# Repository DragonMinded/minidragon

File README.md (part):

# MiniDragon

Schematics, hardware simulator and software files for the MiniDragon CPU. This is a from-scratch CPU that I designed and am implementing using transistors, capacitors, resistors and diodes. The goal is to make an 8-bit CPU that could be used for general-purpose computing. There are a lot of toy instruction sets floating around on the web. I chose instead to design my own, loosely based off of the PDP and 6502. It is a single accumulator design with a pair of 16-bit stack pointers and a pair of temporary 8-bit registers. Instructions are 8 bits, operands are 8 bits from memory, temporary registers or immediate, and running software can access all 16 bits of memory available to the CPU. Eventually, I want the assembled CPU along with some external RAM, ROM and a serial interface chip to be self-hosting. For that, the boot ROM includes a serial montor with a line assembler and disassembler.

## Layout

The layout is separated into logical components:

 * Microcode counter. This keeps track of what microcode in the current instruction we are operating on.
 * Instruction decoder logic. This consists of an instruction register and a series of ROM boards made out of jumpers. This uses the microcode counter as well as its own internal combinatorial logic to select one instruction and output control signals to the rest of the CPU.
 * Registers. These exist on various busses, and their input/output is controlled by the instruction decoder logic's control signals.
 * Constant circuits. These can output either a zero or an immediate value sign extended from the current instruction register. Their operation is controlled by the instruction decoder's control signals.
 * ALU. This is built out of a series of smaller components on its own internal bus. Selection of which operation as well as which input is controlled via the instruction decoder logic's control signals.
 * Flags handling. This consists of a few registers to hold flags generated by the ALU and put them on the data bus when appropriate. This is controlled via the control signal lines much like the rest of the non-instruction decoder components.
 * Memory interface. This provides the glue so that the CPU can be seen as having a set of address and data lines as well as an output enable and write enable line, much like a traditional non-SOC CPU.

### Internal Busses

 * 16-bit data bus. Most registers can only read from or write to the lower 8 bits of this bus, but some can also output their value to the upper 8 bits. Various 16-bit registers are able to read the entire 16-bit bus, and this is how the upper bits of the instruction pointer and stack pointers can be read. The lower 8 bits of this will feed the external data IO lines.
 * 16-bit address bus. This feeds the external address requests by the CPU and is driven by both the instruction pointer and stack pointers.
 * 16-bit ALU source bus. This allows the ALU A source to be controlled, so that various 16-bit registers we want to add/subtract from don't need to be placed in a temporary location.

### Registers

 * 16-bit instruction pointer register (IP), holding the address of the current instruction in memory. Its value can be placed on the address bus or ALU input bus and it can read from the data bus. Software can jump relative to the current instruction, as well as pushing the current IP to the stack (controlled by the PC combined register), pop the IP from the stack or jump to an immediate 16 bit address.
 * 8-bit instruction register (IR), holding the current instruction that was fetched from memory. It is write-only and feeds microcode decoding logic, but can read from the data bus. Software cannot directly set this, but memory is modifiable so self-modifying code is possible.
 * 8-bit accumulator register (A), holding the current accumulated result. It can read from and write to the data bus, and it can output to the ALU input bus. Many instructions available to software can directly manipulate this register. Its value can be moved to and from the P and C registers as well as added to the combined PC register, allowing it to be used for indirect memory address modes as well.
 * 8-bit ALU temporary register (B), holding a temporary value from the bus. It can read from and write to the data bus. Its output is also hardcoded to the second input of the ALU. Software has no capability to modify this register and it is used by various microcodes to accomplish virtually all CPU operations. When the ALU is operating on a 16-bit number, the B register will be sign-extended to 16 bits.
 * 8-bit memory page register (P) and 8-bit memory cell register (C), together holding a 16-bit address. The P and C registers can individually read from the data bus, and the combined PC value can be output to the address bus or the ALU input bus. Software can write to the P and C registers from the A register and can use the combined PC register contents to load from and store to memory. Some ALU operations allow the memory address pointed at by the PC register to be used as an operand for ALU operations against the accumulator (A). The current value of the instruction pointer (IP) can be pushed to or popped from memory referred to by this register. The current value of the shadow PC combined register can also be pushed to or popped from memory referred to by this register.
 * 8-bit shadow page register (SP) and 8-bit shadow cell register (SC), together holding a 16-bit address referred to as SPC. This is not directly addressable, but its current value can be pushed to or popped from the location pointed at by the PC register, and a SWAP instruction allows software to swap the PC and SPC registers.
 * 8-bit CPU data register (D), holding temporary values when the CPU is pushing or popping a 16-bit value off of the stack (PC). We could use the A register for this, but I wanted to make sure that the accumulator was not clobbered when performing stack operations. This is not user readable or writeable.
 * 8-bit temporary registers (U and V), available to the programmer for various operations. These can be moved to from A, swapped to from A or each other, loaded from and stored to memory, and can be used as operands for ALU operations against the accumulator (A).
 * 3-bit flags register, containing a carry flag (CF), a zero flag (ZF) and a shadow PC flag (PC). Software cannot directly set or clear the carry or zero flags, but both carry and zero flags are set appropriately when carrying out any ALU-based operation which sources from and stores to the A register. It is not directly readable by software but there exist skip instructions that allow software to conditionally execute a particular instruction if either CF or ZF is set or cleared. Additionally, several ALU operations allow using the carry flag as an input to chain operations together for 16 and 32 bit arithmetic. The PC flag is toggleable using a special SWAP instruction.

### Instructions

 * JRI - Jump relative to immediate sign-extended + 1. Assembler also supports labels. Can jump 32 forward or backward relative to next instruction. Specifically designed such that "JRI 0" jumps to the next instruction and is encoded as all zeros.
 * LOADI - Load immediate stored in next memory cell to A. Can load any 8-bit value. Skips over that value after executing since it is not a valid instruction.
 * ADDI - Add immediate sign-extended to A, no carry. Can add values between -32 and 31. Affects ZF and CF.
 * INV - Bitwise invert A. Affects ZF and CF.
 * NEG - Twos compliment negate A register. Affects ZF and CF, as if it was implemented as an "INV" followed by an "ADDI 1".
 * SHL - Shift A left by 1, setting the bottom bit to 0, set carry to top bit shifted out. Affects ZF and CF.
 * SHR - Shift A right by 1, setting the top bit to 0, set carry to bottom bit shifted out. Affects ZF and CF.
 * RCL - Shift A left by 1, setting bottom bit to the carry flag, set carry to top bit shifted out. Affects ZF and CF.
 * RCR - Shift A right by 1, setting top bit to the carry flag, set carry to bottom bit shifted out. Affects ZF and CF.
 * ROL - Shift A left by 1, setting the bottom bit to the shifted out top bit, set carry to top bit shifted out. Affects ZF and CF.
 * ROR - Shift A right by 1, setting the top bit to the shifted our bottom bit, set carry to bottom bit shifted out. Affects ZF and CF.
 * ADD - Add contents of memory location PC to A register. Affects ZF and CF.
 * ADC - Add contents of memory location PC to A register, with carry in from flags. Affects ZF and CF.
 * AND - And contents of memory location PC against A register. Affects ZF and CF.
 * OR - Or contents of memory location PC against A register. Affects ZF and CF.
 * XOR - XOR contents of memory location PC against A register. Affects ZF and CF.
 * CMP - Compare contents of memory location PC against A register. Affects ZF and CF.
 * ADDU - Add contents of U to A register. Affects ZF and CF.
 * ADCU - Add contents of U to A register, with carry in from flags. Affects ZF and CF.
 * ANDU - And contents of U against A register. Affects ZF and CF.
 * ORU - Or contents of U against A register. Affects ZF and CF.
 * XORU - XOR contents of U against A register. Affects ZF and CF.
 * CMPU - Compare contents of U against A register. Affects ZF and CF.
 * ADDV - Add contents of V to A register. Affects ZF and CF.
 * ADCV - Add contents of V to A register, with carry in from flags. Affects ZF and CF.
 * ANDV - And contents of V against A register. Affects ZF and CF.
 * ORV - Or contents of V against A register. Affects ZF and CF.
 * XORV - XOR contents of V against A register. Affects ZF and CF.
 * CMPV - Compare contents of V against A register. Affects ZF and CF.
 * ADDPCI - Add immediate to PC. Can add any value between 1 and 32 inclusive. Since we only have the capability of sign-extending the bottom 4 or 6 bits of an instruction to use as an immediate, this intentionally chooses an instruction prefix which sets the 6th bit to 0, in order to simplify decoding logic as well as keep the immediate register simple. This is why there is a separate ADDPCI and SUBPCI instruction.
 * SUBPCI - Subtract immediate from PC. Can subtract any value between 1 and 32 inclusive. Much like ADDPCI, this uses a clever trick where the 6th bit in the instruction prefix is set to 1, in order to correctly sign-extend the immediate.
 * ADDPC - Add A register sign-extended from 8 to 16 bits to the PC register.
 * ATOP - Load contents of A register to P.
 * ATOC - Load contents of A register to C.
 * PTOA - Load contents of P register to A.
 * CTOA - Load contents of C register to A.
 * ATOU - Load contents of A register to U.
 * ATOV - Load contents of A register to V.
 * UTOA - Load contents of U register to A.
 * VTOA - Load contents of V register to A.
 * LOADA - Load contents of memory location pointed at by PC to A register.
 * STOREA - Store contents of A register to memory location pointed at by PC.
 * LOADU - Load contents of memory location pointed at by PC to U register.
 * STOREU - Store contents of U register to memory location pointed at by PC.
 * LOADV - Load contents of memory location pointed at by PC to V register.
 * STOREV - Store contents of V register to memory location pointed at by PC.
 * SKIPIF - Skip next instruction if carry/zero flag set/cleared. To save on decoding logic, the lower 3 bits of the SKIPIF instruction feed combinatorial logic in the flags register. This leaves us with four undefined instructions which would, if executed, choose to operate on either both or neither of the carry and zero flag simultaneously.
 * LNGJUMP - Jumps to address stored in memory location IP + 1 and IP + 2, stored in big-endian.  Skips over the two values after executing since they are not valid instructions.
 * SWAPAU - Swap contents of A and U registers.
 * SWAPAV - Swap contents of A and V registers.
 * SWAPUV - Swap contents of U and V registers.
 * SWAPPC - Swap PC and SPC registers, making the current PC into the shadow PC and vice versa.
 * PUSHIP - Subtracts two from PC, stores IP + immediate into location PC and PC + 1 big endian. Immediate can be a positive integer between 0 and 7 inclusive and is often non-zero in order to store the correct return address of a subroutine call.
 * POPIP - Jumps to data stored in memory location PC and PC + 1 big endian, adds 2 to PC.
 * PUSHSPC - Subtracts two from PC, stores SPC into location PC and PC + 1 big endian.
 * POPSPC - Loads SPC with value stored in memory location PC and PC + 1 big endian, adds 2 to PC.

### Assembler-Provided Macros

For convenience of programming without too much hassle, several assembler macros which are encoded to a series of the above instructions are available:

 * NOP - Perform no operation. Implemented as "JRI 0", which as noted above is encoded as a null byte.
 * HALT - Jump to self, loop forever. Implemented as "JRI -1".
 * ZERO - Zero the contents of A. Implemented as "LOADI 0".
 * SETPC - Set immediate value to PC register, clobbering A register. Sets PC to full 16-bit value. Implemented as a pair of "LOADI" instructions followed by the appropriate "ATOP" and "ATOC". Takes an optional second parameter which is applied as an integer offset to the 16-bit value.
 * INCPC - Add 1 to PC. Implemented as "ADDPCI 1".
 * DECPC - Subtract 1 from PC. Implemented as "SUBPCI 1".
 * STOREI - Stores immediate value to memory pointed at by PC register, clobbering A register. Stores full 8-bit value to memory. Implemented as a "LOADI" followed by a "STOREA".
 * INC - Increment A register. Implemented as an "ADDI 1".
 * DEC - Decrement A register. Implemented as an "ADDI -1".
 * RET - Return from subroutine (identical to POPIP).
 * JRIZ - Jump relative if zero flag set. Implemented using "SKIPIF" and "JRI".
 * JRINZ - Jump relative if zero flag not set. Implemented using "SKIPIF" and "JRI".
 * JRIC - Jump relative if carry flag set. Implemented using "SKIPIF" and "JRI".
 * JRINC - Jump relative if carry flag not set. Implemented using "SKIPIF" and "JRI".
 * LNGJUMPZ - Jump to address if zero flag set. Implemented using "SKIPIF", "JRI" and "LNGJUMP".
 * LNGJUMPNZ - Jump to address if zero flag not set. Implemented using "SKIPIF", "JRI" and "LNGJUMP".
 * LNGJUMPC - Jump to address if carry flag set. Implemented using "SKIPIF", "JRI" and "LNGJUMP".
 * LNGJUMPNC - Jump to address if carry flag not set. Implemented using "SKIPIF", "JRI" and "LNGJUMP".
 * CALL - Subtracts two from PC, stores the next instruction after this instruction to PC, then jumps to the immediate address. Return from this using “RET”. Implemented using a "PUSHIP" and a "LNGJUMP".
 * CALLRI - Subtracts two from PC, stores the next instruction after this instruction to PC, then jumps to the relative offset from the next instruction. Return from this using “RET”. Implemented using a "PUSHIP" and a "JRI" instruction, meaning it is only useful for subroutines located close in memory. However, it can save several bytes.
 * PUSH x - Subtracts operand size from PC, stores the value of A/U/V/IP/SPC into the memory location PC. This is simply a virtual instruction that maps to "STOREA", "STOREU", "STOREV", "PUSHIP" or "PUSHSPC", so that the correct instruction doesn't have to be remembered.
 * PUSHI - Subtracts 1 from PC, stores immediate to memory location PC, clobbering A register. Implmented as a "DECPC" followed by a "STOREI" macro.
 * PUSHADDR - Subtracts 1 from PC, stores low byte of 16-bit immediate value to memory location PC, clobbering A register. Then subtracts 1 again from the PC, stores the high byte of 16-bit immediate value to memory location PC, clobbering the A register again. Implemented as a pair of "DECPC" and "STOREI" macros. Takes an optional second parameter which is applied as an integer offset to the 16-bit value.
 * POP x - Loads the value of memory location PC into A/U/V/IP/SPC, adds operand size to PC. Works identically to "PUSH x" as a virtual instruction alias to several concrete instructions.
 * LOAD x - Loads the value pointed at in memory by PC to A/U/V. Alias for the various concrete load instructions, similar to "PUSH x" and "POP x".
 * STORE x - Stores the value in A/U/V into the memory location pointed at by PC. Alias for the various concrete store instructions, similar to "PUSH x" and "POP x".
 * SWAP x, y - Swaps the contents of a pair of registers. Valid pairs are either from A/U/V or PC/SPC. Alias for the various concrete swap instructions, similar to "PUSH x", "POP x", "LOAD x" and "STORE x".
 * MOV x, y - Moves the contents of the x register into the y register. Any register A/U/V/P/C can be moved to or from as long as one of the operands is the A register. Alias for the various concrete load instructions, similar to "SWAP x, y".

### Opcode Layout

The 8-bit space for a single opcode is split up in order to make it possible to decode instructions using the least amount of logic. There are some holes where future instructions might be added. For now, undefined instructions will produce undefined behavior in the CPU. As currently implemented, the control logic will output all 1's for all control signals of undefined or un-mapped instructions. For this layout, the following conventions are used:

 * Register name - Register names listed directly refer to the value of that register. So, `A + 1` would refer to an operation that takes the value of A and adds 1.
 * `>` - Right carat, implies that the result of the operation on the left is stored to register/location on the right.
 * `[` and `]` - Dereference. This implies that the value of what is inside the `[]` is an address where we will store. So `1 > [PC]` implies that the value of "1" would be stored to the 8-bit memory location referenced by the PC combined register.
 * `{` and `}` - Register operand from the opcode itself. Currently, register operands are defined as follows:
   * `00` - Undefined, no register mapping.
   * `01` - U register.
   * `10` - V register.
   * `11` - SRAM pointed at by PC register.

<pre>
opcpde            description                         implementation                 mnemonic        alias
----------------------------------------------------------------------------------------------------------

<b>y y y y y y y y   immediate op</b>
0 0 x x x x x x   jump to immediate offset            IP + imm + 1 > IP              JRI x
0 1 x x x x x x   add immediate to A                  A + imm -> A                   ADDI x

<b>1 0 0 y y y y y   stack immediate op</b> †1
1 0 0 0 0 x x x   push IP + immediate                 PC - 2 > PC, IP + imm > [PC]   PUSHIP x        PUSH IP + x

<b>1 0 0 s s y y y   arithmetic op with operand</b> †2
1 0 0 s s 0 0 0   compare against [PC]/U/V            A > A                          CMP/CMPU/CMPV
1 0 0 s s 0 0 1   add from [PC]/U/V                   A + {ss} > A                   ADD/ADDU/ADDV
1 0 0 s s 0 1 0   add with carry from [PC]/U/V        A + {ss} + CF > A              ADC/ADCU/ADCV
1 0 0 s s 0 1 1   and from [PC]/U/V                   A & {ss} > A                   AND/ANDU/ANDV
1 0 0 s s 1 0 0   or from [PC]/U/V                    A | {ss} > A                   OR/ORU/ORV
1 0 0 s s 1 0 1   xor from [PC]/U/V                   A ^ {ss} > A                   XOR/XORU/XORV
1 0 0 s s 1 1 0   <i>see tables below</i>
1 0 0 s s 1 1 1   <i>see tables below</i>

<b>1 0 0 s s y y y   arithmetic op against U</b>
1 0 0 0 1 0 0 0   <i>compare A against U</i>
1 0 0 0 1 0 0 1   <i>add from U</i>
1 0 0 0 1 0 1 0   <i>add with carry from U</i>
1 0 0 0 1 0 1 1   <i>and from U</i>
1 0 0 0 1 1 0 0   <i>or from U</i>
1 0 0 0 1 1 0 1   <i>xor from U</i>
1 0 0 0 1 1 1 0   rotate left A                       A << 1 + ((A >> 7) & 0x01) > A ROL
1 0 0 0 1 1 1 1   rotate right A                      A >> 1 + ((A << 7) & 0x80) > A ROR

<b>1 0 0 s s y y y   arithmetic op against V</b>
1 0 0 1 0 0 0 0   <i>compare A against V</i>
1 0 0 1 0 0 0 1   <i>add from V</i>
1 0 0 1 0 0 1 0   <i>add with carry from V</i>
1 0 0 1 0 0 1 1   <i>and from V</i>
1 0 0 1 0 1 0 0   <i>or from V</i>
1 0 0 1 0 1 0 1   <i>xor from V</i>
1 0 0 1 0 1 1 0   rotate left with carry A            A << 1 + CF > A                RCL
1 0 0 1 0 1 1 1   rotate right with carry A           A >> 1 + (CF << 7) > A         RCR

<b>1 0 0 s s y y y   arithmetic op against [PC]</b>
1 0 0 1 1 0 0 0   <i>compare A against [PC]</i>
1 0 0 1 1 0 0 1   <i>add from [PC]</i>
1 0 0 1 1 0 1 0   <i>add with carry from [PC]</i>
1 0 0 1 1 0 1 1   <i>and from [PC]</i>
1 0 0 1 1 1 0 0   <i>or from [PC]</i>
1 0 0 1 1 1 0 1   <i>xor from [PC]</i>
1 0 0 1 1 1 1 0   shift left A                        A << 1 > A                     SHL
1 0 0 1 1 1 1 1   shift right A                       A >> 1 > A                     SHR

<b>1 0 1 y y y y y   pc subtract op</b> †3
1 0 1 x x x x x   Subtract immediate from PC          PC - imm - 1 > PC              SUBPCI x

<b>1 1 0 y y y y y   pc add op</b> †4
1 1 0 x x x x x   Add immediate to PC                 PC + imm + 1 > PC              ADDPCI x

<b>1 1 1 0 0 y y y   register op</b>
1 1 1 0 0 0 0 0   load from address P + C to U        [P | C] > U                    LOADU           LOAD U
1 1 1 0 0 0 0 1   store to address P + C from U       U > [P | C]                    STOREU          STORE U
1 1 1 0 0 0 1 0   load from address P + C to V        [P | C] > V                    LOADV           LOAD V
1 1 1 0 0 0 1 1   store to address P + C from V       V > [P | C]                    STOREV          STORE V
1 1 1 0 0 1 0 0   swap A and U                        A > U, U > A                   SWAPAU          SWAP A, U/SWAP U, A
1 1 1 0 0 1 0 1   swap A and V                        A > V, V > A                   SWAPAV          SWAP A, V/SWAP V, A
1 1 1 0 0 1 1 0   swap U and V                        U > V, V > U                   SWAPUV          SWAP U, V/SWAP V, U
1 1 1 0 0 1 1 1   swap PC and SPC                     PC > SPC, SPC > PC             SWAPPC          SWAP PC, SPC/SWAP SPC, PC

<b>1 1 1 0 1 y y y   memory op</b>
1 1 1 0 1 0 0 0   load page register from A           A > P                          ATOP            MOV A, P
1 1 1 0 1 0 0 1   load cell register from A           A > C                          ATOC            MOV A, C
1 1 1 0 1 0 1 0   store page register to A            P > A                          PTOA            MOV P, A
1 1 1 0 1 0 1 1   store cell register to A            C > A                          CTOA            MOV C, A
1 1 1 0 1 1 0 0   load U register from A              A > U                          ATOU            MOV A, U
1 1 1 0 1 1 0 1   load V register from A              A > V                          ATOV            MOV A, V
1 1 1 0 1 1 1 0   store U register to A               U > A                          UTOA            MOV U, A
1 1 1 0 1 1 1 1   store V register to A               V > A                          VTOA            MOV V, A

<b>1 1 1 1 0 y y y   status op</b> †5
1 1 1 1 0 0 0 0   invert A                            ~A > A                         INV
1 1 1 1 0 0 0 1   negate A                            ~A + 1 > A                     NEG
1 1 1 1 0 0 1 0   skip next instruction if CF         IP + 1 + CF > IP               SKIPIF CF
1 1 1 1 0 0 1 1   skip next instruction if !CF        IP + 1 + !CF > IP              SKIPIF !CF
1 1 1 1 0 1 0 0   skip next instruction if ZF         IP + 1 + ZF > IP               SKIPIF ZF
1 1 1 1 0 1 0 1   skip next instruction if !ZF        IP + 1 + !ZF > IP              SKIPIF !ZF
1 1 1 1 0 1 1 0   invert A                            ~A > A                         INV
1 1 1 1 0 1 1 1   negate A                            ~A + 1 > A                     NEG

<b>1 1 1 1 1 y y y   stack op</b>
1 1 1 1 1 0 0 0   jump to immediate                   [IP + 1] > IP                  LNGJUMP x
1 1 1 1 1 0 0 1   load immediate                      [IP + 1] -> A                  LOADI x
1 1 1 1 1 0 1 0   add to PC                           PC + A > PC                    ADDPC
1 1 1 1 1 0 1 1   pop IP                              [PC] > IP, PC + 2 > PC         POPIP           POP IP
1 1 1 1 1 1 0 0   push SPC                            PC - 2 > PC, SPC > [PC]        PUSHSPC         PUSH SPC
1 1 1 1 1 1 0 1   pop SPC                             [PC] > SPC, PC + 2 > PC        POPSPC          POP SPC
1 1 1 1 1 1 1 0   load from address P + C             [P | C] > A                    LOADA           LOAD A
1 1 1 1 1 1 1 1   store to address P + C              A > [P | C]                    STOREA          STORE A
</pre>

 * †1 This instruction occupies the same space as the ALU operations. This is why register operand {00} is undefined. The instruction decoder will not select the ALU operation decoder board when "PUSHIP" is detected.
 * †2 This might be slightly misleading, given that the register operand {00} is not only undefined but also not mapped to ALU operations. See †1 for details.
 * †3 Due to only being able to sign-extend the lower 4 or 6 bits of an instruction, this cleverly puts itself into an instuction slot where the 6th bit is 1.
 * †4 Due to only being able to sign-extend the lower 4 or 6 bits of an instruction, this cleverly puts itself into an instuction slot where the 6th bit is 0.
 * †5 I've shoved some arithmetic instructions that do not use a "B" operand here. We decode them versus a SKIPIF by doing an XOR/EQUALITY on the 2nd and 3rd bit, making them map to two places in the ISA. When in SKIPIF mode, we use the lower 3 bits as selector signals for combinatorial logic. The lowest bit is used as an "invert selected flags signal" bit, and the next two bits are used as "CF select" and "ZF select". This is why we can map unrelated instructions to when the last two bits are 00 or 11, since those would map to "neither CF or ZF" and "both CF and ZF" respectively.

## Design Concessions

As was the case with many 8-bit CPUs in the last century, this CPU does not have included memory, either volatile or non-volatile. It instead will assume an external chip or set of chips present on its external address and data bus. These chips, in the interest of practicality, will be standard TTL-compatible DIP package chips providing 16KB of SRAM, 30KB of ROM, 16KB of removable cartridge space and 2KB of IO address space in which I am currently planning to place an 8-bit serial chip to talk to a VT-100 terminal. Other plans include an RTCRAM chip for settings and clock support, a GPIO chip, a cartridge interface including a cartridge control peripheral and room for additional expansion chips.

Due to the sheer number of parts involved in making a register as well as the control logic needed in order to select registers for ALU operations, there are only two scratch registers. Most intermediate values must therefore be stored on the stack. Various core library operations were sped up significantly when adding the U and V registers as slower stack manipulation operations could be dropped. Additional speedups as well as easier implementation of core functionality could be realized by adding additional scratch registers. However, this would increase the complexity of the instruction decoding logic and require a necessary juggling of instructions in the above table.

Similarly, due to the complexity of such a circuit, no number comparison instructions are present. Instead, comparison functions are implemented in the stdlib by bitwise comparing two numbers from top to bottom bit. This makes a lot of functions such as integer conversion and division functions much slower than they need to be. Due to this, I'm considering possibly adding a compare instruction to the ALU in place of the currently empty instruction slot in the ALU instruction block. INV used to occupy that spot but has been moved to one of the unused opcodes in the status op block in anticipation of a future addition. If I implement a hardware CMP I would have room to implement a hardware NEG as well. I've experimented with this on a separate branch and the gains are significant. Alternatively, its possible to design an external math coprocessor. This is similar to contemporary CPUs with a floating point or math coprocessor so would not be out of the question. If this happens, the standard library should be updated to call the coprocessor instead of performing comparisons, multiplication and division on-CPU.

Because of the complexity of designing such a system from scratch there are a lot of inefficiencies in how the various circuits are assembled. In many cases, buffers are not actually necessary and add to propagation delay. In order to make the project manageable by a single creature I've decided to sacrifice any sort of speed for modularity. This will result in a CPU that can theoretically only operate at a clock cycle of ~100KHz and in practice operates at ~18KHz. If I was to be a lot more dilligent I could probably get this up into the several hundered or even megahertz level, but it isn't worth it. Perhaps in a second, miniaturized TTL-only iteration?

### Memory Layout

As alluded to above, the MiniDragon can access a full 64k of address space because all memory operations are based on either the IP or the SP registers. No banking is necessary so no special hardware is required in order for software to access the full range of memory. The MiniDragon provides no custom IO port instructions so all hardware access must be performed through memory-mapped IO. Because virtually all hardware chips designed in the era MiniDragon is targetting only used a few registers, that means the address space for hardware itself can be very small. MiniDragon takes advantage of this by minimizing the memory-mapped IO portion of its address space.

The boot ROM is mapped to the bottom 30KB of addressable memory. Because 30KB EEPROMs do not exist, a 32KB EEPROM will be used to provide this, with the top 2KB invisible to the CPU. The boot ROM is mapped to the beginning of the address space because MiniDragon's reset vector is 0x0000. The next 2KB of memory will be reserved for memory-mapped IO. 2KB was chosen specifically because the MiniDragon is slated to allow for 8 expansion cards for IO expansion circuits. 2KB divides by 8 cleanly, meaning that each expansion card will receive 256 bytes of memory to place any necessary registers. In practice this will be accomplished by a 3 to 8 address bus decoder chip providing a chip select signal to each card, along with 8 address lines, 8 bidirectional data lines and a few miscellaneous signals. The top 32KB of memory will be mapped to 16KB of cartridge space and a pair of 8KB SRAM chips. This makes setting the stack pointer relatively convenient since it can be placed at 0x0000 during boot and the first PUSH instruction will wrap it around to the top of memory where the SRAM chip sits.

## Build Progress

As I continue with both the physical and virtual implementations of MiniDragon its been useful to break down the work into more manageable tasks. A side benefit is that I get to see things moving closer to completion at a much smaller scale. As of last calculation, I am 86% finished with the whole project.

### Hardware

As a whole, the hardware side of MiniDragon is 97% complete.

 - instruction decoder: 79% complete
    - Design work and diagramming for the instruction decoder core, including microcode counting, distribution logic, demultiplexing logic and associated glue is finished. Diagramming for exact connections to various instruction ROM boards is not complete. Of the 57 instructions (56 real instructions and a microcode board for the shared load instruction step) 45 instructions are fully hooked in and the shared load step is wired up. The instruction decoder core is fully built and integrated into the physical build.
 - special registers: 100% complete
   - All design work and diagramming for necessry circuits is completed. Registers that can be read in order to perform conditional logic as well as source immediate values are completed and fully integrated onto the physical build.
 - general purpose registers: 100% complete
   - All design work and diagramming for the eight general purpose registers is completed. All registers (A, B, D, U, V, IP, PC and SPC) are built and fully integrated into the physical build.
 - ALU: 100% complete
   - The ALU core is completely designed, laid out and documented. Tested and fabricated designs for ADD, INV, OR, AND, XOR, SHL and SHR are integrated into the physical layout. The ALU is decomposed into seven core functions that each generate their own output and carry flag, along with a shared zero flag generator and a carry flag selector circuit.
 - memory interface: 100% complete
   - The MiniDragon CPU is designed to appear like a standard 80's TTL CPU from external components' perspective. This means 16 output "pins" for address lines, 8 bidirectional "pins" for data lines, and a few crucial control signals brought out. These signals include a negated write enable and read enable signal, a negated reset signal and a buffered clock signal. It should be noted that all of these signals (save for the clock) are asynchronous, but the write enable line does pulse low with the clock transition since various memory chips use the low to high transition as their write signal. All signals are TTL level and impedance compatible, and the bidirectional data bus uses TTL-compatible tri-state logic.
   - Additional circuitry that is not technically part of MiniDragon but will be necessary for its execution include a serial chip for IO, glue logic to support address decoding, a ROM chip and an SRAM chip to provide nonvolatile and volatile storage. These will be built using off-the-shelf TTL-compatible 7400 logic and ASICs since they aren't part of the CPU itself and their progress is detailed under the external boards bullet below.
 - power distribution: 100% complete
   - I went with an adjustable 5V switching mode power supply that can supply the necessary amperage (5+ amps estimated at this point) along with a few digital readouts sprinkled across the board for fine adjustments. The circuits are fairly sensitive to core voltage being at or slightly above 4.75V so the main power supply is turned up to about 5.60V to accomodate voltage sag in the power distribution circuits.
 - debugging boards: 100% complete
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
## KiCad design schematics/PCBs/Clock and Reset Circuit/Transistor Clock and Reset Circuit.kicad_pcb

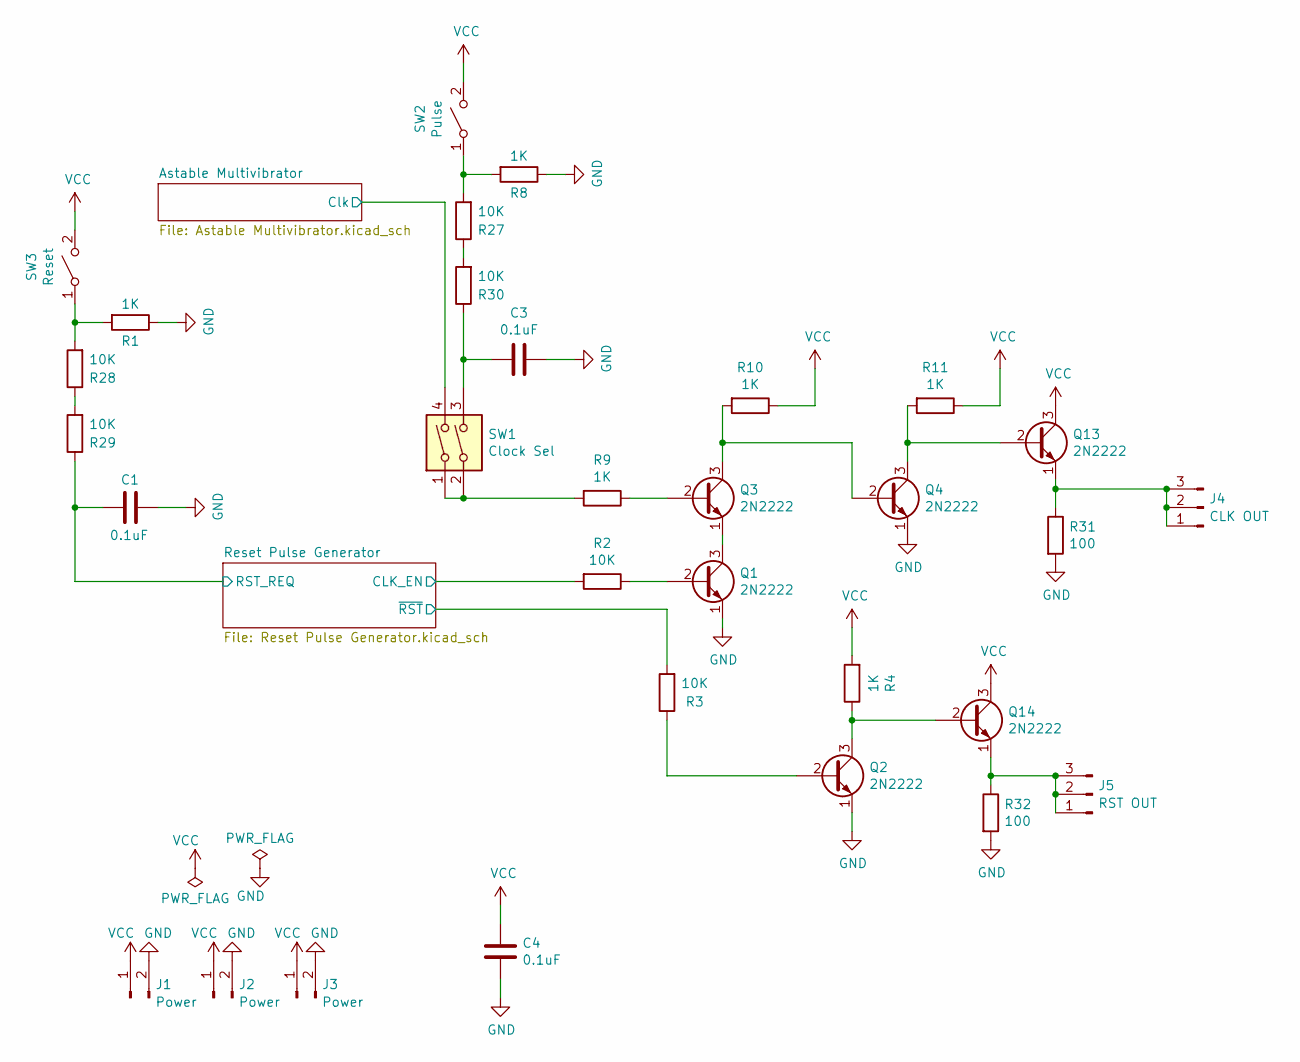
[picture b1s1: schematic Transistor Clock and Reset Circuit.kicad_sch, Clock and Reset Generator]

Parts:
C1, C3, C4: 0.1uF; C_Disc_D4.3mm_W1.9mm_P5.00mm
J1, J2, J3: Power; PinHeader_1x02_P2.54mm_Vertical
J4: CLK OUT; PinHeader_1x03_P2.54mm_Vertical
J5: RST OUT; PinHeader_1x03_P2.54mm_Vertical
Q1, Q2, Q3, Q4, Q13, Q14: 2N2222; TO-92_Inline
R1, R4, R8, R9, R10, R11: 1K; R_Axial_DIN0309_L9.0mm_D3.2mm_P12.70mm_Horizontal
R2, R3, R27, R28, R29, R30: 10K; R_Axial_DIN0309_L9.0mm_D3.2mm_P12.70mm_Horizontal
R31, R32: 100; R_Axial_DIN0309_L9.0mm_D3.2mm_P12.70mm_Horizontal
SW1: Clock Sel; SW_DIP_SPSTx02_Slide_9.78x7.26mm_W7.62mm_P2.54mm
SW2: Pulse; SW_PUSH_6mm_H5mm
SW3: Reset; SW_PUSH_6mm_H5mm

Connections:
/Astable Multivibrator/Clk: SW1.4; also elsewhere on the board
/Reset Pulse Generator/CLK_EN: R2.2; also elsewhere on the board
/Reset Pulse Generator/RST_REQ: C1.1, R29.1; also elsewhere on the board
/Reset Pulse Generator/~RST: R3.2; also elsewhere on the board
GND: C1.2, C3.1, C4.2, J1.2, J2.2, J3.2, Q1.1 (E), Q2.1 (E), Q4.1 (E), R1.1, R8.1, R31.2, R32.2; also elsewhere on the board
unnamed: C3.2, R30.1, SW1.3
unnamed: J4.1, J4.2, J4.3, Q13.1 (E), R31.1
unnamed: J5.1, J5.2, J5.3, Q14.1 (E), R32.1
unnamed: Q1.2 (B), R2.1
unnamed: Q1.3 (C), Q3.1 (E)
unnamed: Q2.2 (B), R3.1
unnamed: Q3.2 (B), R9.1
unnamed: Q3.3 (C), Q4.2 (B), R10.2
unnamed: Q4.3 (C), Q13.2 (B), R11.2
unnamed: Q2.3 (C), Q14.2 (B), R4.1
unnamed: R9.2, SW1.1, SW1.2
unnamed: R27.1, R30.2
unnamed: R28.1, R29.2
unnamed: R8.2, R27.2, SW2.1 (A)
unnamed: R1.2, R28.2, SW3.1 (A)
VCC: C4.1, J1.1, J2.1, J3.1, Q13.3 (C), Q14.3 (C), R4.2, R10.1, R11.1, SW2.2 (B), SW3.2 (B); also elsewhere on the board

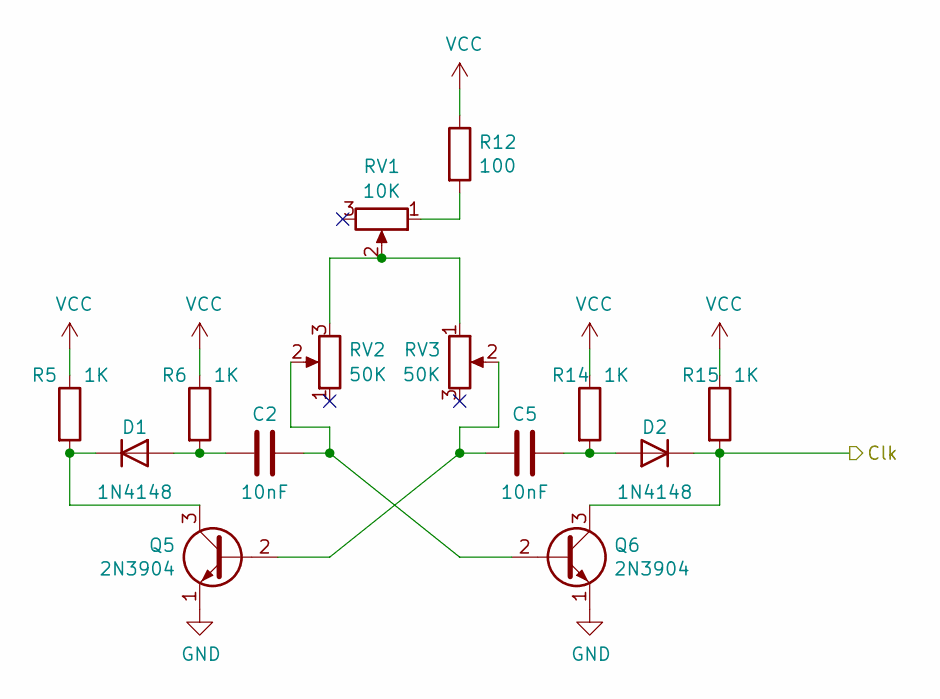
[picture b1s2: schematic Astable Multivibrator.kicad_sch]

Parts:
C2, C5: 10nF; C_Disc_D4.3mm_W1.9mm_P5.00mm
D1, D2: 1N4148; D_DO-35_SOD27_P7.62mm_Horizontal
Q5, Q6: 2N3904; TO-92_Inline
R5, R6, R14, R15: 1K; R_Axial_DIN0309_L9.0mm_D3.2mm_P12.70mm_Horizontal
R12: 100; R_Axial_DIN0309_L9.0mm_D3.2mm_P12.70mm_Horizontal
RV1: 10K; Minidragon Potentiometer
RV2, RV3: 50K; Minidragon Potentiometer

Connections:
/Astable Multivibrator/Clk: D2.1 (K), Q6.3 (C), R15.2; also elsewhere on the board
GND: Q5.1 (E), Q6.1 (E); also elsewhere on the board
unnamed: C2.2, D1.2 (A), R6.2
unnamed: D1.1 (K), Q5.3 (C), R5.2
unnamed: C5.1, D2.2 (A), R14.2
unnamed: C5.2, Q5.2 (B), RV3.2
unnamed: C2.1, Q6.2 (B), RV2.2
unnamed: R12.2, RV1.1
unnamed: RV1.2, RV2.3, RV3.1
VCC: R5.1, R6.1, R12.1, R14.1, R15.1; also elsewhere on the board

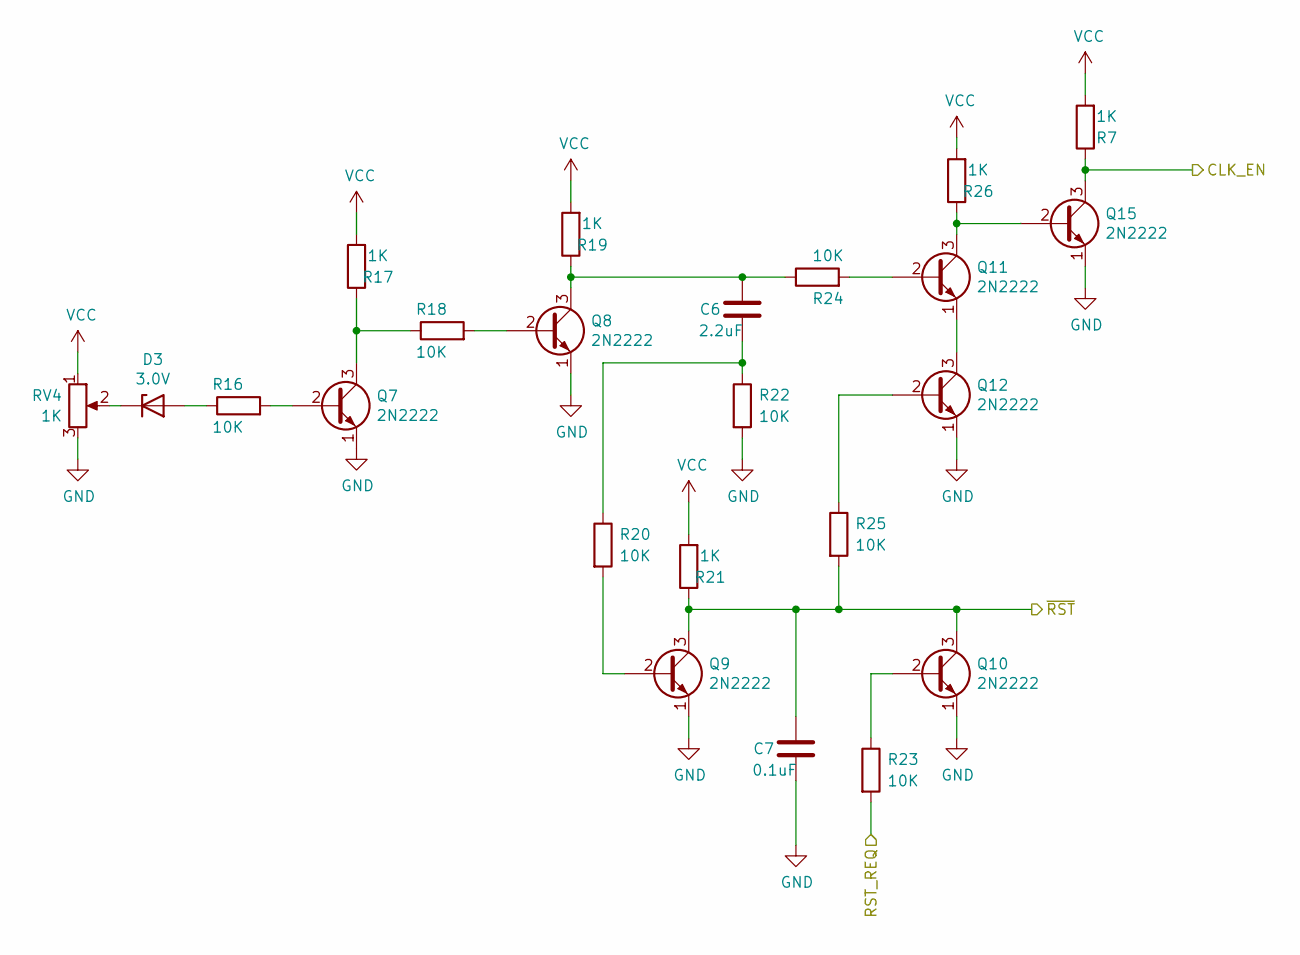
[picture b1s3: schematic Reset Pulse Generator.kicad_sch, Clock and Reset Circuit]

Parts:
C6: 2.2uF; C_Disc_D4.3mm_W1.9mm_P5.00mm
C7: 0.1uF; C_Disc_D4.3mm_W1.9mm_P5.00mm
D3: 3.0V; D_DO-35_SOD27_P7.62mm_Horizontal
Q7, Q8, Q9, Q10, Q11, Q12, Q15: 2N2222; TO-92_Inline
R7, R17, R19, R21, R26: 1K; R_Axial_DIN0309_L9.0mm_D3.2mm_P12.70mm_Horizontal
R16, R18, R20, R22, R23, R24, R25: 10K; R_Axial_DIN0309_L9.0mm_D3.2mm_P12.70mm_Horizontal
RV4: 1K; Minidragon Potentiometer

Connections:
/Reset Pulse Generator/CLK_EN: Q15.3 (C), R7.1; also elsewhere on the board
/Reset Pulse Generator/RST_REQ: R23.2; also elsewhere on the board
/Reset Pulse Generator/~RST: C7.1, Q9.3 (C), Q10.3 (C), R21.1, R25.2; also elsewhere on the board
GND: C7.2, Q7.1 (E), Q8.1 (E), Q9.1 (E), Q10.1 (E), Q12.1 (E), Q15.1 (E), R22.2, RV4.3; also elsewhere on the board
unnamed: C6.2, R20.1, R22.1
unnamed: D3.2 (A), R16.1
unnamed: D3.1 (K), RV4.2
unnamed: Q7.2 (B), R16.2
unnamed: Q7.3 (C), R17.1, R18.1
unnamed: Q8.2 (B), R18.2
unnamed: C6.1, Q8.3 (C), R19.1, R24.1
unnamed: Q9.2 (B), R20.2
unnamed: Q10.2 (B), R23.1
unnamed: Q11.2 (B), R24.2
unnamed: Q11.3 (C), Q15.2 (B), R26.1
unnamed: Q11.1 (E), Q12.3 (C)
unnamed: Q12.2 (B), R25.1
VCC: R7.2, R17.2, R19.2, R21.2, R26.2, RV4.1; also elsewhere on the board

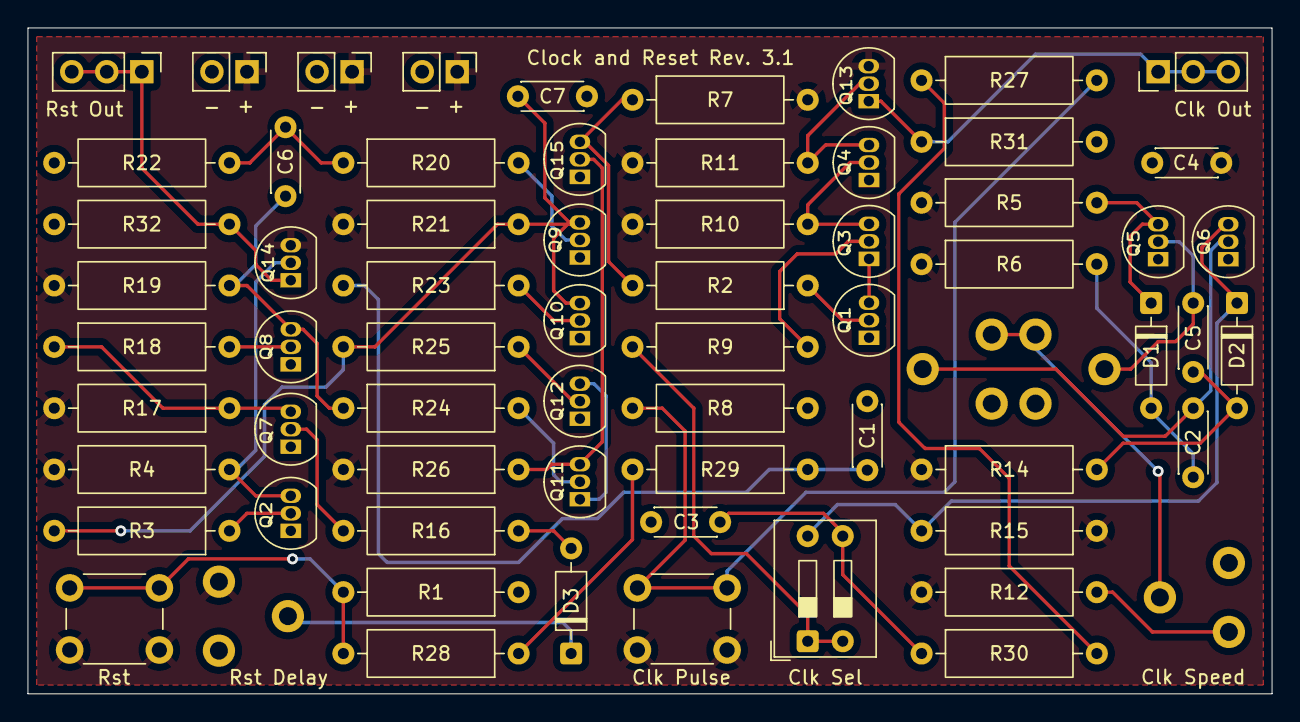
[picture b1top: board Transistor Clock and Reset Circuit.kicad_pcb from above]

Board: 2 copper layers, 90.2 x 48.3 mm, 68 parts (0 on the bottom side), 41 nets.

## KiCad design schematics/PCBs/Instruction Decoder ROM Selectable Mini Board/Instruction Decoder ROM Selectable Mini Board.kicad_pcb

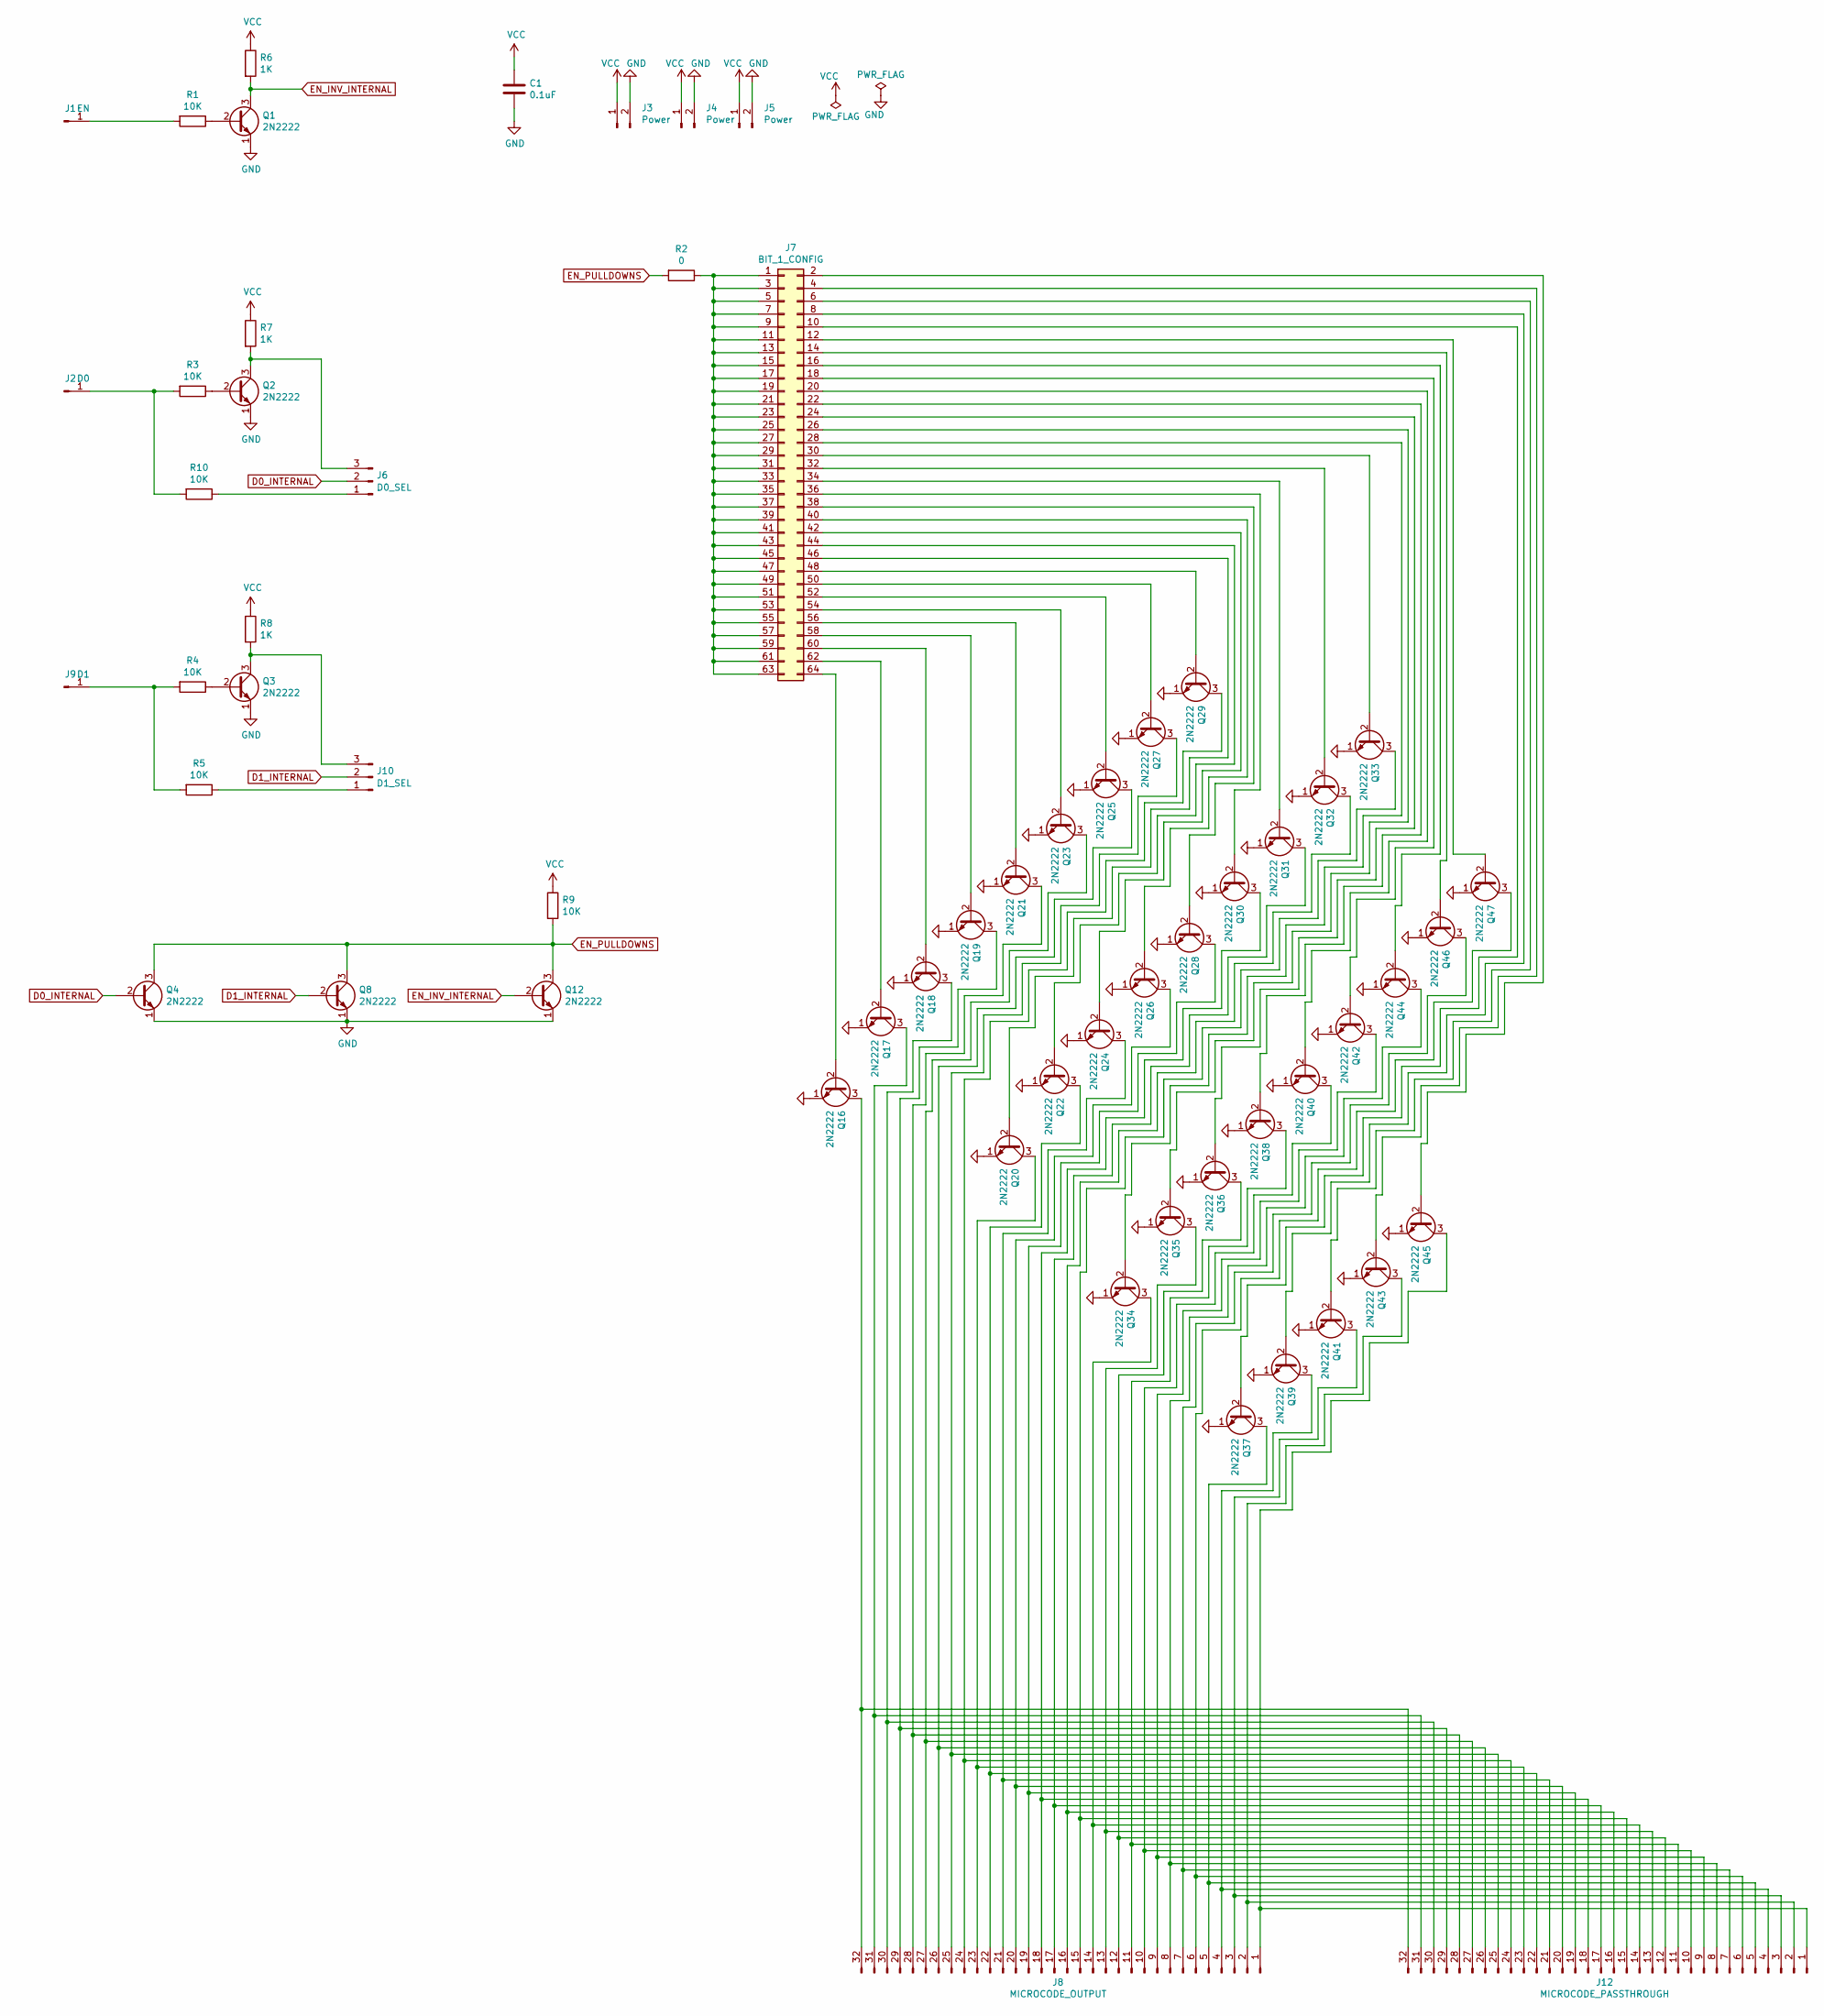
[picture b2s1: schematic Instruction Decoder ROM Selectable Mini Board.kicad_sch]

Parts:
C1: 0.1uF; C_Disc_D4.3mm_W1.9mm_P5.00mm
J1: EN; PinHeader_1x01_P2.54mm_Vertical
J2: D0; PinHeader_1x01_P2.54mm_Vertical
J3, J4, J5: Power; PinHeader_1x02_P2.54mm_Vertical
J6: D0_SEL; PinHeader_1x03_P2.54mm_Vertical
J7: BIT_1_CONFIG; PinHeader_2x32_P2.54mm_Vertical
J8: MICROCODE_OUTPUT; PinHeader_1x32_P2.54mm_Vertical
J9: D1; PinHeader_1x01_P2.54mm_Vertical
J10: D1_SEL; PinHeader_1x03_P2.54mm_Vertical
J12: MICROCODE_PASSTHROUGH; PinHeader_1x32_P2.54mm_Vertical
Q1, Q2, Q3, Q4, Q8, Q12, Q16, Q17, Q18, Q19, Q20, Q21, Q22, Q23, Q24, Q25, Q26, Q27, Q28, Q29, Q30, Q31, Q32, Q33, Q34, Q35, Q36, Q37, Q38, Q39, Q40, Q41, Q42, Q43, Q44, Q45, Q46, Q47: 2N2222; TO-92_Inline
R1, R3, R4, R5, R9, R10: 10K; R_Axial_DIN0309_L9.0mm_D3.2mm_P12.70mm_Horizontal
R2: 0; R_Axial_DIN0309_L9.0mm_D3.2mm_P12.70mm_Horizontal
R6, R7, R8: 1K; R_Axial_DIN0309_L9.0mm_D3.2mm_P12.70mm_Horizontal

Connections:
D0_INTERNAL: J6.2, Q4.2 (B)
D1_INTERNAL: J10.2, Q8.2 (B)
EN_INV_INTERNAL: Q1.3 (C), Q12.2 (B), R6.2
EN_PULLDOWNS: Q4.3 (C), Q8.3 (C), Q12.3 (C), R2.2, R9.2
GND: C1.2, J3.2, J4.2, J5.2, Q1.1 (E), Q2.1 (E), Q3.1 (E), Q4.1 (E), Q8.1 (E), Q12.1 (E), Q16.1 (E), Q17.1 (E), Q18.1 (E), Q19.1 (E), Q20.1 (E), Q21.1 (E), Q22.1 (E), Q23.1 (E), Q24.1 (E), Q25.1 (E), Q26.1 (E), Q27.1 (E), Q28.1 (E), Q29.1 (E), Q30.1 (E), Q31.1 (E), Q32.1 (E), Q33.1 (E), Q34.1 (E), Q35.1 (E), Q36.1 (E), Q37.1 (E), Q38.1 (E), Q39.1 (E), Q40.1 (E), Q41.1 (E), Q42.1 (E), Q43.1 (E), Q44.1 (E), Q45.1 (E), Q46.1 (E), Q47.1 (E)
unnamed: J1.1, R1.2
unnamed: J2.1, R3.2, R10.2
unnamed: J6.1, R10.1
unnamed: J6.3, Q2.3 (C), R7.2
unnamed: J7.1, J7.3, J7.5, J7.7, J7.9, J7.11, J7.13, J7.15, J7.17, J7.19, J7.21, J7.23, J7.25, J7.27, J7.29, J7.31, J7.33, J7.35, J7.37, J7.39, J7.41, J7.43, J7.45, J7.47, J7.49, J7.51, J7.53, J7.55, J7.57, J7.59, J7.61, J7.63, R2.1
unnamed: J7.2, Q45.2 (B)
unnamed: J7.4, Q43.2 (B)
unnamed: J7.6, Q41.2 (B)
unnamed: J7.8, Q39.2 (B)
unnamed: J7.10, Q37.2 (B)
unnamed: J7.12, Q47.2 (B)
unnamed: J7.14, Q46.2 (B)
unnamed: J7.16, Q44.2 (B)
unnamed: J7.18, Q42.2 (B)
unnamed: J7.20, Q40.2 (B)
unnamed: J7.22, Q38.2 (B)
unnamed: J7.24, Q36.2 (B)
unnamed: J7.26, Q35.2 (B)
unnamed: J7.28, Q34.2 (B)
unnamed: J7.30, Q33.2 (B)
unnamed: J7.32, Q32.2 (B)
unnamed: J7.34, Q31.2 (B)
unnamed: J7.36, Q30.2 (B)
unnamed: J7.38, Q28.2 (B)
unnamed: J7.40, Q26.2 (B)
unnamed: J7.42, Q24.2 (B)
unnamed: J7.44, Q22.2 (B)
unnamed: J7.46, Q20.2 (B)
unnamed: J7.48, Q29.2 (B)
unnamed: J7.50, Q27.2 (B)
unnamed: J7.52, Q25.2 (B)
unnamed: J7.54, Q23.2 (B)
unnamed: J7.56, Q21.2 (B)
unnamed: J7.58, Q19.2 (B)
unnamed: J7.60, Q18.2 (B)
unnamed: J7.62, Q17.2 (B)
unnamed: J7.64, Q16.2 (B)
unnamed: J9.1, R4.2, R5.2
unnamed: J10.1, R5.1
unnamed: J10.3, Q3.3 (C), R8.2
unnamed: J8.1, J12.1, Q45.3 (C)
unnamed: J8.2, J12.2, Q43.3 (C)
unnamed: J8.3, J12.3, Q41.3 (C)
unnamed: J8.4, J12.4, Q39.3 (C)
unnamed: J8.5, J12.5, Q37.3 (C)
unnamed: J8.6, J12.6, Q47.3 (C)
unnamed: J8.7, J12.7, Q46.3 (C)
unnamed: J8.8, J12.8, Q44.3 (C)
unnamed: J8.9, J12.9, Q42.3 (C)
unnamed: J8.10, J12.10, Q40.3 (C)
unnamed: J8.11, J12.11, Q38.3 (C)
unnamed: J8.12, J12.12, Q36.3 (C)
unnamed: J8.13, J12.13, Q35.3 (C)
unnamed: J8.14, J12.14, Q34.3 (C)
unnamed: J8.15, J12.15, Q33.3 (C)
unnamed: J8.16, J12.16, Q32.3 (C)
unnamed: J8.17, J12.17, Q31.3 (C)
unnamed: J8.18, J12.18, Q30.3 (C)
unnamed: J8.19, J12.19, Q28.3 (C)
unnamed: J8.20, J12.20, Q26.3 (C)
unnamed: J8.21, J12.21, Q24.3 (C)
unnamed: J8.22, J12.22, Q22.3 (C)
unnamed: J8.23, J12.23, Q20.3 (C)
unnamed: J8.24, J12.24, Q29.3 (C)
unnamed: J8.25, J12.25, Q27.3 (C)
unnamed: J8.26, J12.26, Q25.3 (C)
unnamed: J8.27, J12.27, Q23.3 (C)
unnamed: J8.28, J12.28, Q21.3 (C)
unnamed: J8.29, J12.29, Q19.3 (C)
unnamed: J8.30, J12.30, Q18.3 (C)
unnamed: J8.31, J12.31, Q17.3 (C)
unnamed: J8.32, J12.32, Q16.3 (C)
unnamed: Q1.2 (B), R1.1
unnamed: Q2.2 (B), R3.1
unnamed: Q3.2 (B), R4.1
VCC: C1.1, J3.1, J4.1, J5.1, R6.1, R7.1, R8.1, R9.1

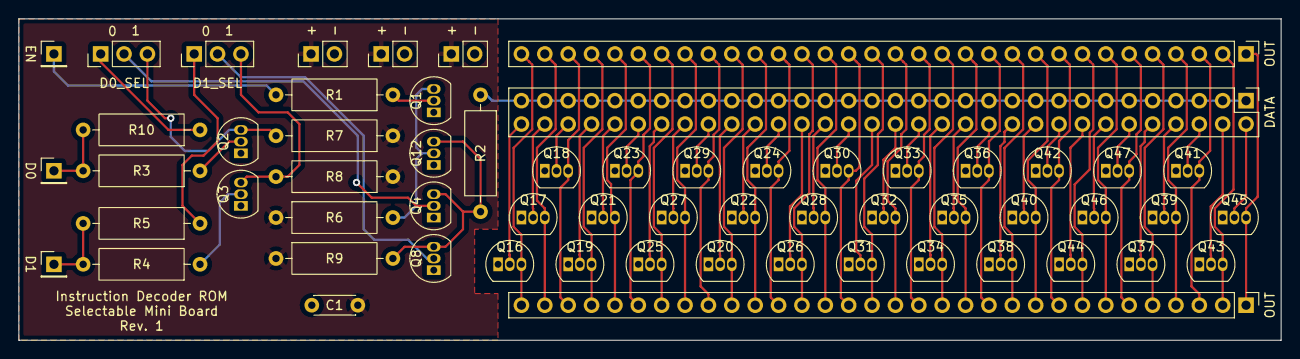
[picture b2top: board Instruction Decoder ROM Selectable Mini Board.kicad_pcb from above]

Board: 2 copper layers, 137.2 x 34.9 mm, 60 parts (0 on the bottom side), 81 nets.
